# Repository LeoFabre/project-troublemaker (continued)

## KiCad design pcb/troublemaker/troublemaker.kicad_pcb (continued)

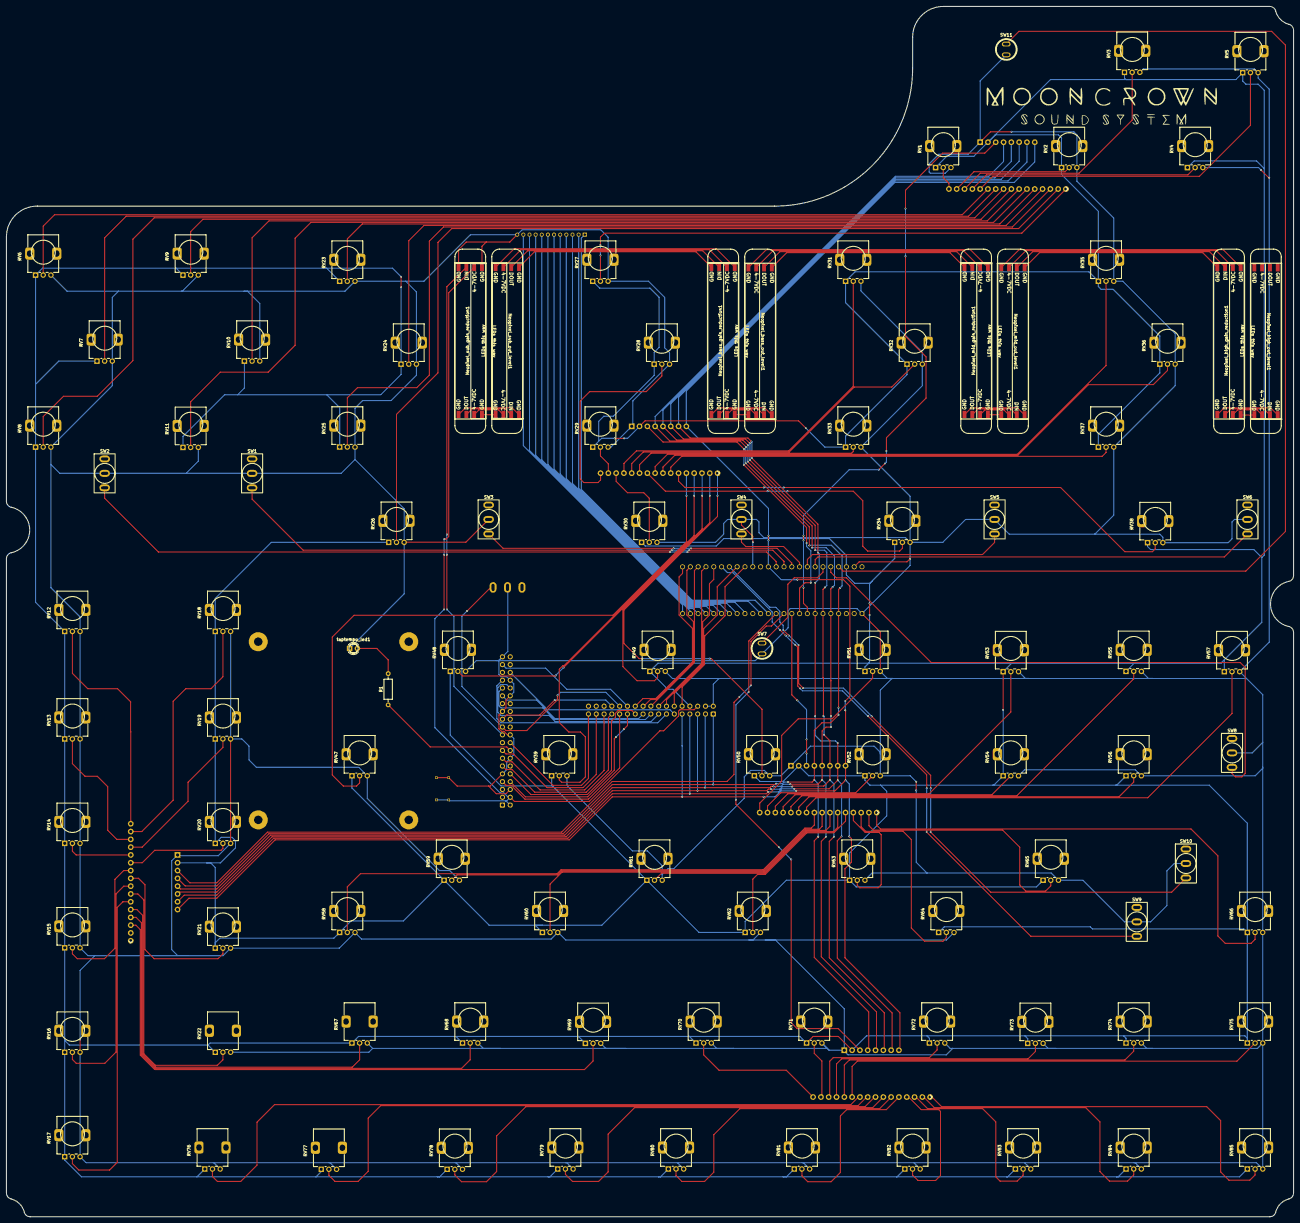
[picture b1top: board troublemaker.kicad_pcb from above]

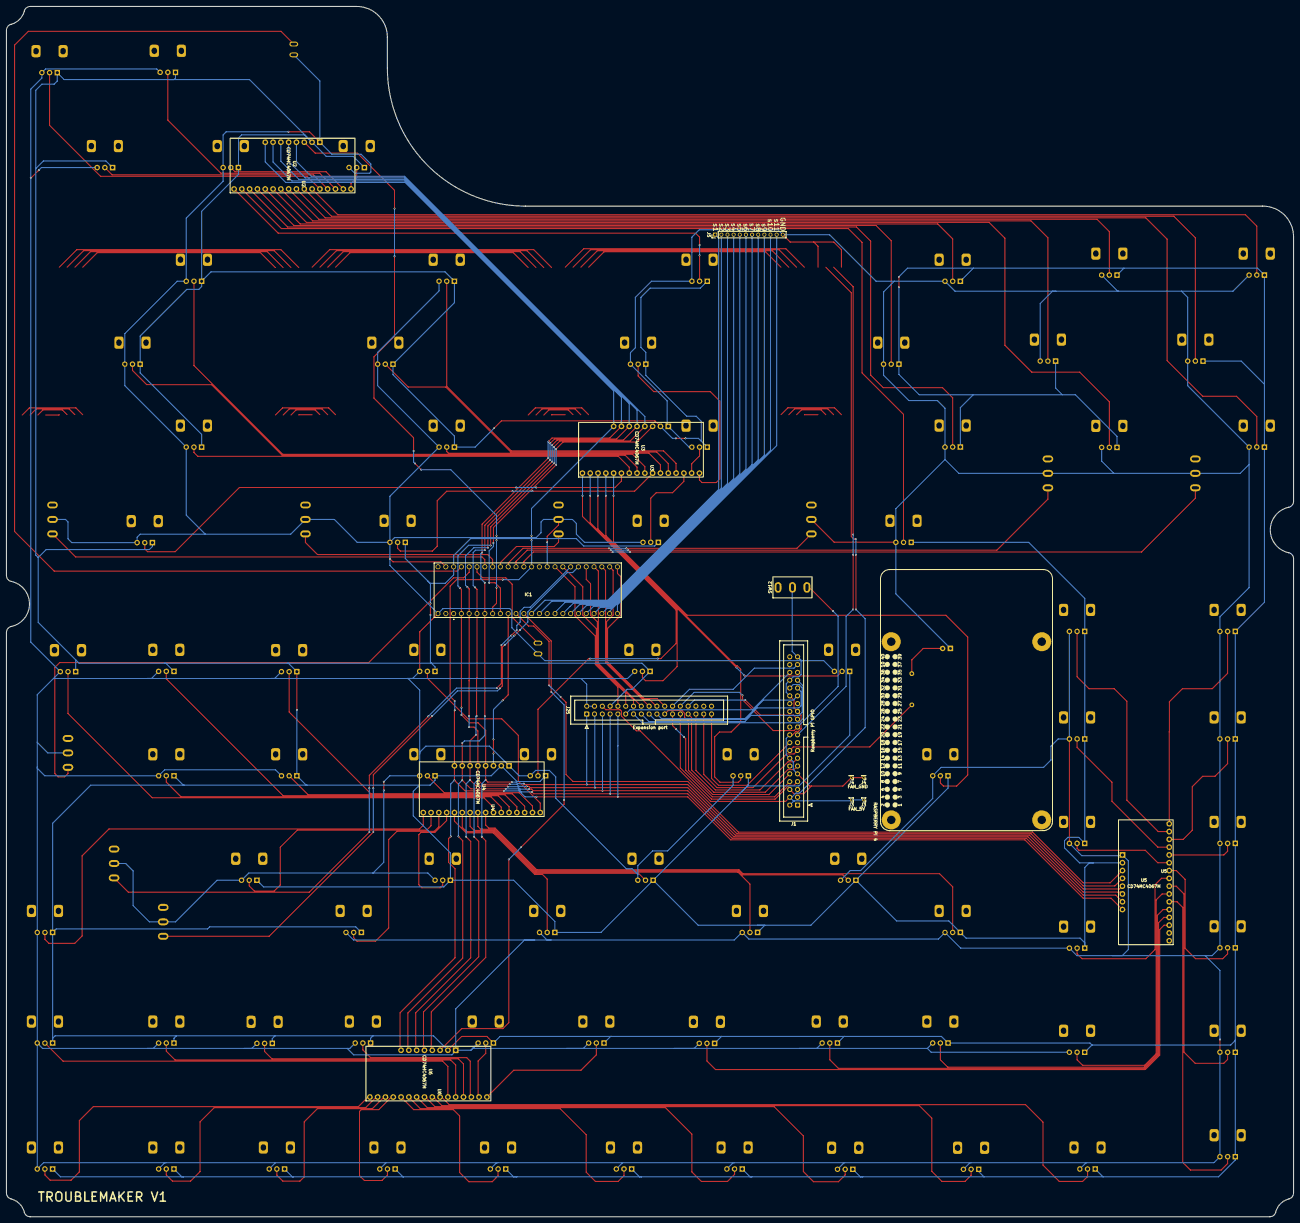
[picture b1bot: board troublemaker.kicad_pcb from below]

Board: 2 copper layers, 419.0 x 394.0 mm, 115 parts (15 on the bottom side), 166 nets.

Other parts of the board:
J3#2: 5V_RPI2_OR_4; PinHeader_1x01_P1.00mm_Vertical
J4#2: GND_RPI34; PinHeader_1x01_P1.00mm_Vertical
RASPBERRY PI 4: RASPBERRY_PI_4B_4GB; MODULE_RASPBERRY_PI_4B_4GB
Ref**: Val**; TestSilkscreen

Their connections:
XT_GND: J4#2.1; also elsewhere on the board
XT_RPi_5v: J3#2.1; also elsewhere on the board

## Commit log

2024-09-15 WIP readme
2024-09-15 moved assets into a folder
2024-09-17 One knob midi controller code
2024-09-17 Potentiometer class
2024-09-18 tech stack diagram pic
2024-10-09 notes and volts lots of pots code adapted to current prototype
2024-10-09 replaced use of MIDI.h with MIDIUSB.h
2024-10-09 trying to figure out why the teensy reboot-loops, using vanilla MidiUSB
2024-10-10 fixed warnings trying with only 8 pots
2024-10-10 Now using Control Surface, 16 pots prototype works
2024-10-10 cleanup
2024-10-15 EQ+Xover prototype code
2024-10-21 kicad schematics v0.1
2024-10-21 Added taptempo led, now using SnapEDA teensy and rpi schemes and footprints
2024-10-22 Added missing stuff on schematic, PCB layout WIP
2024-10-22 Added gitignores
2024-10-22 added pcb autosave to gitignore
2024-10-22 Fixed some issues with the PCB
2024-10-22 Added Fusion360 design file (WIP)
2024-10-23 Fixed IC footprints having edge cuts
2024-10-23 JLCPCB DRC, pots are connected to muxers, rearranged scheme, added missing LED resistor and pin header
2024-10-24 GND + 3v3 connections
2024-10-24 Added symbols and footprints
2024-10-24 small routing fixes, saved project file after changing lib paths
2024-10-24 Working on routing the muxers
2024-10-26 All connections done
2024-10-26 Fixed DRC errors
2024-10-26 fixed missing connections
2024-10-26 Removed pads from RPI footprint, added some text to jumpers
2024-10-27 Removed capacitors as I already have them on the breakout board. Small reroutes.
2024-10-27 updated enclosure design
2024-10-28 added expansion port and GPIO socket
2024-10-29 added mooncrown logo
2024-10-29 Cleaned PCB traces
2024-10-29 Last PCB finishes and cleanups, added gerber files
2024-11-17 PCB midi controller code (to be tested)
2024-11-17 PCB midi controller code refactor
2024-11-17 Fixed muxers signal pin and button type
2024-11-18 Fixed bad rebase
2024-11-18 Fixed sampler buttons being CC
2024-11-18 Grouped controls channels by plugin, now using 0 to N
2024-11-19 Inverted pots and xover switches
2024-11-19 Added sushi config and plugin dumps
2024-11-19 Set minimum delay time to 0.1 to avoid larsen
2024-11-19 Fixed pots deadzone
2024-11-21 Fixed roar config
2024-11-21 Fixed "highass" setting lmao
2024-11-21 Removed JuceAutoFilter from config bc of stereo bug (?)
2024-11-21 Some midi & mapping fixes, added echo lowcut
2024-11-21 Fixed echo filter, remapped eq ranges
2024-11-21 Added echo filter, various mapping fixes
2025-01-15 Mapped gain controls using inverse-logarithmic function
2025-01-15 Mapped gain controls max gain back to 0.83
2025-01-15 Replaced gain plugins with my own
2025-01-15 Fixed bad config Back to old method for pots controlling my own gain plugin
2025-01-16 Updated config to match new multiband comp
2025-01-17 Fixed echo filter bad midi mapping
2025-01-17 MIDI Controller now reacts to sysex message "F0 7D 01 02 03 F7" and sends current state in a burst of midi messages
2025-01-17 Renamed Roar pots to match design update
2025-09-28 Update StrangeReturns config
2025-10-31 Sushi Config - add Master track, with EQ proof of concept (will be replaced with a custom VST)
2025-10-31 Mapped tap tempo button
2026-06-10 Update project status to abandoned in README
